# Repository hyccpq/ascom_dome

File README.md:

# Ascom Alpaca ESP32 Dome Board

ESP32-S3 firmware for controlling a roll-off-roof / sliding dome top through the ASCOM Alpaca protocol.

This trimmed version keeps only the Dome control path:

- Alpaca Dome discovery and API endpoints
- Web page for Dome state and Open / Close / Halt commands
- Web setup for Dome pins and timeout settings
- WiFi manager connection flow
- OTA firmware and filesystem updates

Switch and CoverCalibrator modules have been removed from the firmware, web UI, SPIFFS defaults, and Alpaca device discovery.

## ESP32-S3 Dome I/O

The current firmware uses fixed GPIO definitions in `src/board_pins.h`:

| Signal | GPIO |
| --- | --- |
| Open command relay trigger | 4 |
| Close command relay trigger | 5 |
| Stop / halt command relay trigger | 6 |
| Open limit input | 7 |
| Close limit input | 8 |
| Reserved rain sensor input | 9 |

The three relay outputs are intended to pulse external isolated trigger inputs for open, close, and stop. The rain sensor header is initialized as an input and reported in diagnostics, but it does not automatically close the dome until the sensor polarity and desired safety behavior are defined.

The web setup page still stores the original dome configuration file for compatibility, but the active control pins are the fixed GPIO constants above.

Detailed hardware notes are in `docs/esp32-s3-dome-board-hardware.md`.

## Build

Install Visual Studio Code and the PlatformIO extension, then open this folder as a PlatformIO project.

From the command line:

```sh
pio run
```

To build the SPIFFS image:

```sh
pio run --target buildfs
```

## First Upload

Use PlatformIO:

1. Upload Filesystem Image
2. Upload firmware

On first boot, connect to the WiFi manager access point and configure the board for your observatory WiFi.

## Web Interface

After the board joins WiFi, open the ESP32 IP address in a browser.

- `/` shows Dome status and Open / Close / Halt controls.
- `/setup` shows Dome configuration.
- `/update` is provided by ElegantOTA for firmware and filesystem updates.

## ASCOM Alpaca

The board listens for Alpaca discovery on UDP `32227` and serves Alpaca device requests on port `4567`.

Only one configured device is advertised:

- Device type: `Dome`
- Device number: `0`

Useful endpoints include:

- `GET /management/apiversions`
- `GET /management/v1/description`
- `GET /management/v1/configureddevices`
- `GET /api/v1/dome/0/shutterstatus`
- `PUT /api/v1/dome/0/openshutter`
- `PUT /api/v1/dome/0/closeshutter`
- `PUT /api/v1/dome/0/abortslew`

## Verification

Current smoke check:

```sh
pio run
```

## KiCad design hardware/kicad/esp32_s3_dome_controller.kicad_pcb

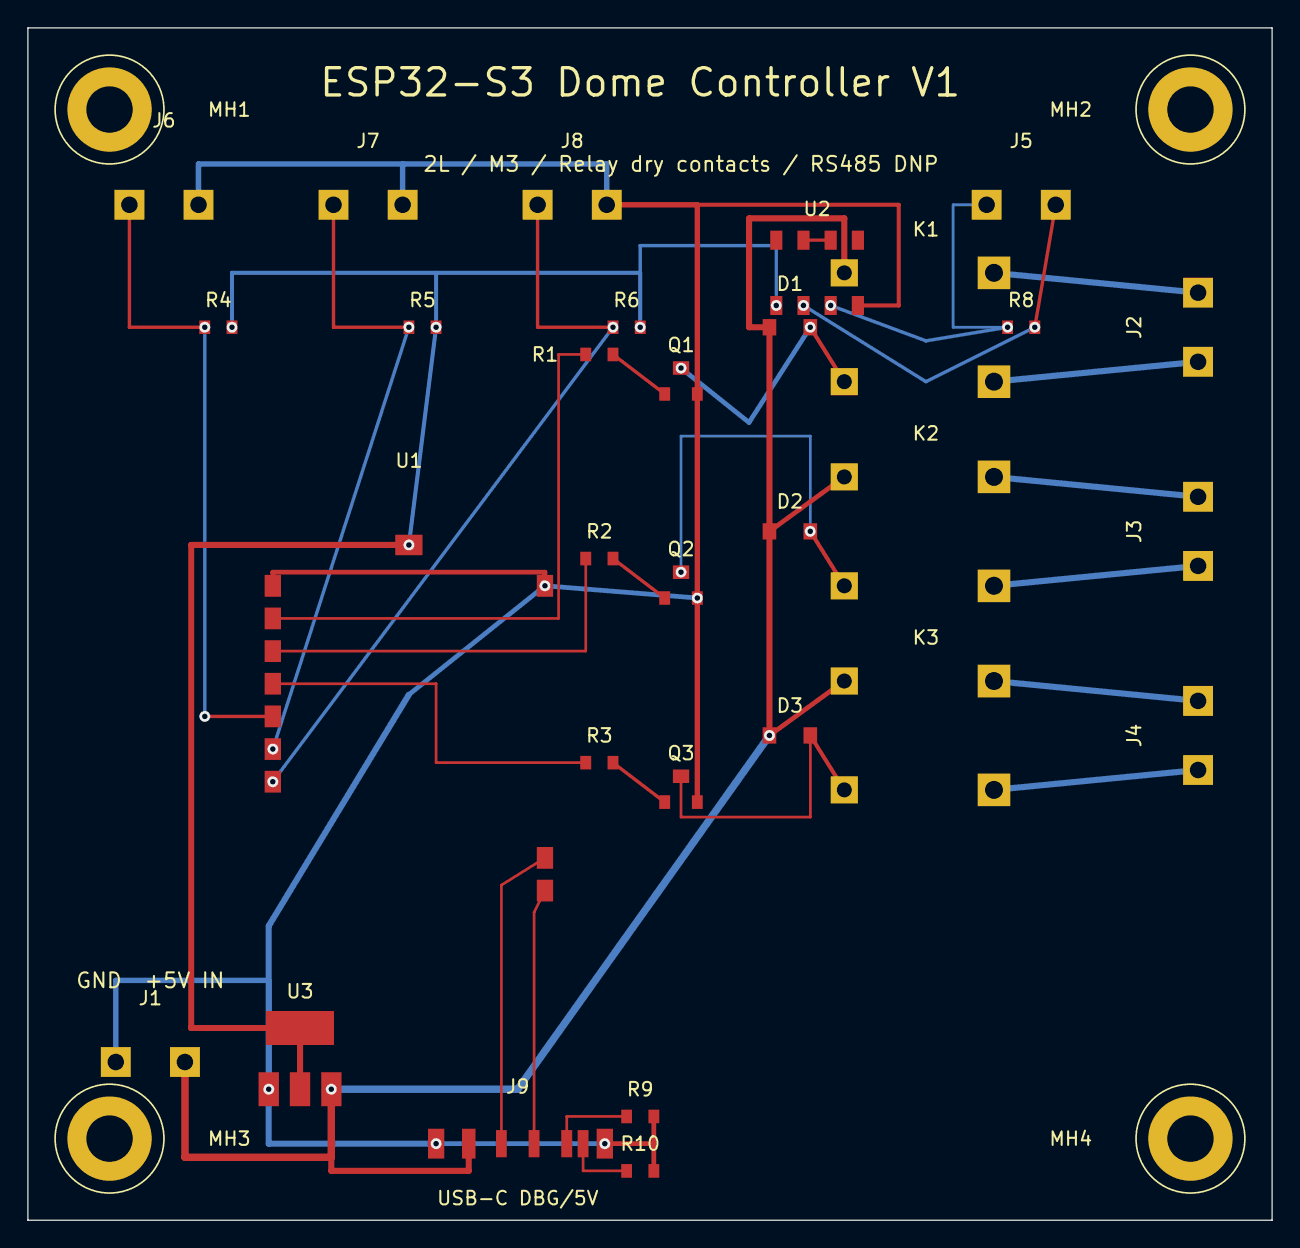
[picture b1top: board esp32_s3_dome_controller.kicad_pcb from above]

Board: 2 copper layers, 91.4 x 87.6 mm, 34 parts (0 on the bottom side), 28 nets.

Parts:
D1: 1N4148/SS14; D1
D2: 1N4148/SS14; D2
D3: 1N4148/SS14; D3
J1: 5V IN; J1
J2: OPEN OUT; J2
J3: CLOSE OUT; J3
J4: STOP OUT; J4
J5: RS485; J5
J6: OPEN LIMIT; J6
J7: CLOSE LIMIT; J7
J8: RAIN; J8
J9: USB-C DEVICE; J9
K1: SRD-05VDC-SL-C; K1
K2: SRD-05VDC-SL-C; K2
K3: SRD-05VDC-SL-C; K3
MH1: M3 NPTH; MH1
MH2: M3 NPTH; MH2
MH3: M3 NPTH; MH3
MH4: M3 NPTH; MH4
Q1: AO3400A; Q1
Q2: AO3400A; Q2
Q3: AO3400A; Q3
R1: 100R; R1
R2: 100R; R2
R3: 100R; R3
R4: 10k pullup; R4
R5: 10k pullup; R5
R6: 10k pullup; R6
R8: 120R DNP; R8
R9: 5.1k; R9
R10: 5.1k; R10
U1: ESP32-S3-WROOM-1; U1
U2: MAX3485; U2
U3: AMS1117-3.3; U3

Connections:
3V3: R4.2, R5.2, R6.2, U1.3V3, U2.8, U3.2, U3.4
5V: D1.1, D2.1, D3.1, J1.2, J9.VBUS, K1.COIL+, K2.COIL+, K3.COIL+, U3.3
CLOSE_COIL_LOW: D2.2, K2.COIL-, Q2.3
CLOSE_COM: J3.2, K2.COM
CLOSE_GATE: Q2.1, R2.2
CLOSE_GPIO5: R2.1, U1.5
CLOSE_LIMIT_GPIO8: J7.1, R5.1, U1.12
CLOSE_NO: J3.1, K2.NO
GND: J1.1, J6.2, J7.2, J8.2, J9.GND1, J9.GND2, Q1.2, Q2.2, Q3.2, R9.2, R10.2, U1.1, U1.40, U2.5, U3.1
OPEN_COIL_LOW: D1.2, K1.COIL-, Q1.3
OPEN_COM: J2.2, K1.COM
OPEN_GATE: Q1.1, R1.2
OPEN_GPIO4: R1.1, U1.4
OPEN_LIMIT_GPIO7: J6.1, R4.1, U1.7
OPEN_NO: J2.1, K1.NO
RAIN_GPIO9: J8.1, R6.1, U1.17
RS485_A: J5.1, R8.1, U2.6
RS485_B: J5.2, R8.2, U2.7
RS485_RE_DE: U2.2, U2.3
STOP_COIL_LOW: D3.2, K3.COIL-, Q3.3
STOP_COM: J4.2, K3.COM
STOP_GATE: Q3.1, R3.2
STOP_GPIO6: R3.1, U1.6
STOP_NO: J4.1, K3.NO
USB_CC1: J9.CC1, R9.1
USB_CC2: J9.CC2, R10.1
USB_D+: J9.D+, U1.20
USB_D-: J9.D-, U1.19

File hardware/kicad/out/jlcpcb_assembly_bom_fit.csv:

Comment,Designator,Footprint,LCSC Part #,JLCPCB Class
ESP32-S3-WROOM-1-N8R8,U1,EasyEDA WIRELM-SMD_ESP32-S3-WROOM-1,C2913201,Extended
AMS1117-3.3,U3,EasyEDA SOT-223-3_L6.5-W3.4-P2.30-LS7.0-BR,C6186,Basic
SRD-05VDC-SL-C,"K1,K2,K3",Relay_THT matched Songle SRD footprint,C35449,Extended
AO3400A,"Q1,Q2,Q3",Package_TO_SOT_SMD:SOT-23,C20917,Basic
1N4148W,"D1,D2,D3",Diode_SMD:D_SOD-123,C81598,Basic
100R,"R1,R2,R3",Resistor_SMD:R_0603_1608Metric,C22775,Basic
10k,"R4,R5,R6",Resistor_SMD:R_0603_1608Metric,C25804,Basic
5.1k,"R9,R10",Resistor_SMD:R_0603_1608Metric,C23186,Basic
5.08mm 2P terminal,J1,TerminalBlock 1x02 P5.08mm,C8465,Extended
5.08mm 2P terminal,"J2,J3,J4",TerminalBlock 1x02 P5.08mm,C8465,Extended
3.81mm 2P terminal,"J6,J7,J8",EasyEDA CONN-TH_P3.81_KF128L-3.81-2P-1,C9900005589,Extended
USB-C receptacle,J9,Connector_USB matching HRO TYPE-C-31-M-12,C165948,Extended

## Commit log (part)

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2026-06-13 Add ESP32-S3 dome board hardware package
